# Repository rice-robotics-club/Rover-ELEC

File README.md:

# Rice Robotics URC Rover

Firmware, software, and hardware for Rice Robotics' [University Rover Challenge](https://urc.marssociety.org/) team.

<!-- TODO: rover photo or banner, e.g.  — keep it under ~500 KB -->

---

## About

The University Rover Challenge (URC) is an international competition, run by the Mars Society, where student teams design and build a Mars rover prototype. The rover competes in field missions such as science sample analysis, equipment servicing, extreme retrieval and delivery, and autonomous navigation. Check the current year's rules for the exact missions.

This repository holds all of our rover work. The current focus is the **2026-2027 season**.

- **Club website:** TODO
- **URC rules:** TODO (link to the current year's rules)

---

## Repository Layout

```
Rover-ELEC/
├── 2024-2025/              # archive
├── 2025-2026/              # archive
├── 2026-2027/              # current season
│   ├── rover-arm/
│   ├── rover-drivetrain/
│   ├── rover-science/
│   ├── rover-communication/
│   ├── rover-power/
│   └── rover-integration/
└── Summer26/               # archive
```

`2024-2025/`, `2025-2026/`, and `Summer26/` are kept as-is for reference. **All new work goes in `2026-2027/`.**

---

## Subsystems

| Subsystem | What it does | Lead |
|---|---|---|
| [rover-arm](2026-2027/rover-arm/) | Controls the Dynamixel and Robstride actuators on the arm for autonomous and teleop tasks | Joshua Aviles |
| [rover-drivetrain](2026-2027/rover-drivetrain/) | Controls the Robstrides on the drivetrain for autonomous and teleop tasks | Joshua Aviles |
| [rover-science](2026-2027/rover-science/) | Control and manage the sensors and actuators needed for science | Sean Drzewiczewski |
| [rover-communication](2026-2027/rover-communication/) | Establish the link between the radios on the rover and the base station | Sam Wilson |
| [rover-power](2026-2027/rover-power/) | Provide and manage the power needed for all subsystems and their individual components | Miles Kammler |
| [rover-integration](2026-2027/rover-integration/) | Connect all subsystems to the onboard computer under a single ROS workspace | Sam Wilson |

Not sure who to ask? Start with the subsystem lead.

---

## Subsystem Structure

Every subsystem except `rover-integration` uses the same layout. If you know one, you know them all. `rover-integration` has its own layout, described in [its README](2026-2027/rover-integration/).

```
rover-<subsystem>/
├── README.md
├── docs/
│   ├── architecture.md
│   ├── hardware.md
│   ├── software.md
│   ├── testing.md
│   └── media/
├── firmware/
│   ├── arduino-core/
│   │   └── <node-name>/
│   │       ├── README.md
│   │       └── <node-name>.ino
│   └── esp-idf/
│       └── <node-name>/
│           ├── README.md
│           ├── platformio.ini
│           └── src/
├── software/
│   ├── rover_<subsystem>_<function>/
│   └── dependencies.md
├── hardware/
│   ├── pcb/
│   └── mechanical/
└── scripts/
```

### What goes where

**`README.md`**: Start here. What the subsystem does, which boards it uses, and how to build and upload.

**`docs/`**: Everything someone needs to understand the subsystem without asking you.
- `architecture.md`: The big picture. Block diagram and how the pieces talk to each other.
- `hardware.md`: Power, wiring, and pinout. "Which wire goes where?"
- `software.md`: ROS 2 nodes, topics, parameters, and how to run them.
- `testing.md`: How things were tested, the results, and how each number was measured.
- `media/`: Small images used in the docs (diagrams, pinouts). Videos and photo dumps go on Google Drive or YouTube, linked from `media/README.md`.

**`firmware/`**: Code that runs on the microcontrollers. Each folder inside is one board's job, named by what it does (`joint-controller`, `power-monitor`), not by chip.
- `arduino-core/`: Arduino code, built and uploaded with the **Arduino IDE**. The `.ino` file must have the same name as its folder.
- `esp-idf/`: ESP-IDF code, built and uploaded with **PlatformIO**. When an Arduino node is ported to ESP-IDF, it keeps the same folder name.

**`software/`**: Code that runs on the Jetson.
- `rover_<subsystem>_<function>/`: One full ROS 2 package per folder (for example, `rover_arm_control`).
- `dependencies.md`: Outside libraries and tools this subsystem uses, with links and versions.

**`hardware/`**: Physical design files.
- `pcb/`: KiCad source files plus fabrication outputs (Gerbers, BOM, PDF schematic).
- `mechanical/`: CAD files, or links to Onshape/Fusion.

**`scripts/`**: Helper scripts for flashing, calibration, parsing logs, and similar tasks.

## Firmware README Template

Every firmware folder (`arduino-core/<node-name>/` or `esp-idf/<node-name>/`) needs a `README.md`. Copy this, fill in the table, and leave the hint comment in if you want (it doesn't show on GitHub).

```markdown
# node-name

Short 1-2 sentence summary of what this firmware does and what it connects to.

<!--
How to fill this in:
- Board: exact name from Tools > Board (Arduino IDE) or "board =" in platformio.ini
- Tool: Arduino IDE version (Help > About), or PlatformIO Core version (run: pio --version)
- Board package / platform: Arduino IDE > Boards Manager version, or "platform =" in platformio.ini
- Libraries: name + version, separated by <br> for multiple, or "None"
- Wiring: link to the pinout in docs/hardware.md
-->

| Field | Value |
|---|---|
| **Board** |  |
| **Tool** |  |
| **Board package / platform** |  |
| **Libraries** |  |
| **Wiring** | [docs/hardware.md](../../../docs/hardware.md) |
```

### Ground rules

- Don't delete folders your subsystem isn't using yet. Leave the stub `README.md` so every subsystem looks the same.
- Arduino IDE is only for `arduino-core/`, and PlatformIO is only for `esp-idf/`.
- Never commit build outputs (`.pio/`, `build/`, `install/`, `log/`) or large videos.

---

## Tech Stack

| Area | Standard |
|---|---|
| Onboard computer | NVIDIA Jetson, Ubuntu 24.04, ROS 2 Jazzy |
| Microcontrollers | Arduino (initial testing only) and ESP-32S |
| Firmware | Arduino core (Arduino IDE) or ESP-IDF (PlatformIO) |
| PCB design | KiCad |
| Mechanical CAD | Onshape |

---

## Getting Started

1. **Install git** and set up your GitHub account. Ask a lead to add you to the repo.
2. **Clone the repo:**
```bash
   git clone https://github.com/rice-robotics-club/Rover-ELEC.git
   cd Rover-ELEC 
```
3. **Install the tools for your subsystem:**
   - **Firmware (Arduino):** [Arduino IDE](https://www.arduino.cc/en/software) + the ESP32 board package
   - **Firmware (ESP-IDF):** [PlatformIO](https://platformio.org/install/ide?install=vscode) in VS Code
   - **ROS 2 / Jetson:** see [`rover-integration/docs/jetson-setup.md`](2026-2027/rover-integration/docs/jetson-setup.md)
   - **PCB:** [KiCad](https://www.kicad.org/download/) TODO (version)
4. **Read your subsystem's README** and [CONTRIBUTING.md](CONTRIBUTING.md) before your first commit.

---

## Contributing

1. Pull the latest `main`.
2. Create a branch: `<subsystem>/<short-description>` (example: `arm/joint-limits`).
3. Commit small, clear changes.
4. Open a pull request into `main`. Your subsystem lead will review it.

Never commit directly to `main`. Full rules are in [CONTRIBUTING.md](CONTRIBUTING.md).

---

## Resources

- **Google Drive (photos, videos, large files):** TODO
- **Discord / Slack:** TODO
- **URC rules:** TODO
- **Team docs / meeting notes:** TODO

---

## License

This project is licensed under the terms in [LICENSE](LICENSE).

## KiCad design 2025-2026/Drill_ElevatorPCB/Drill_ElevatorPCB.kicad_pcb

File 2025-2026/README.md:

# Rover-ELEC
Repo for all you rover elec fiends

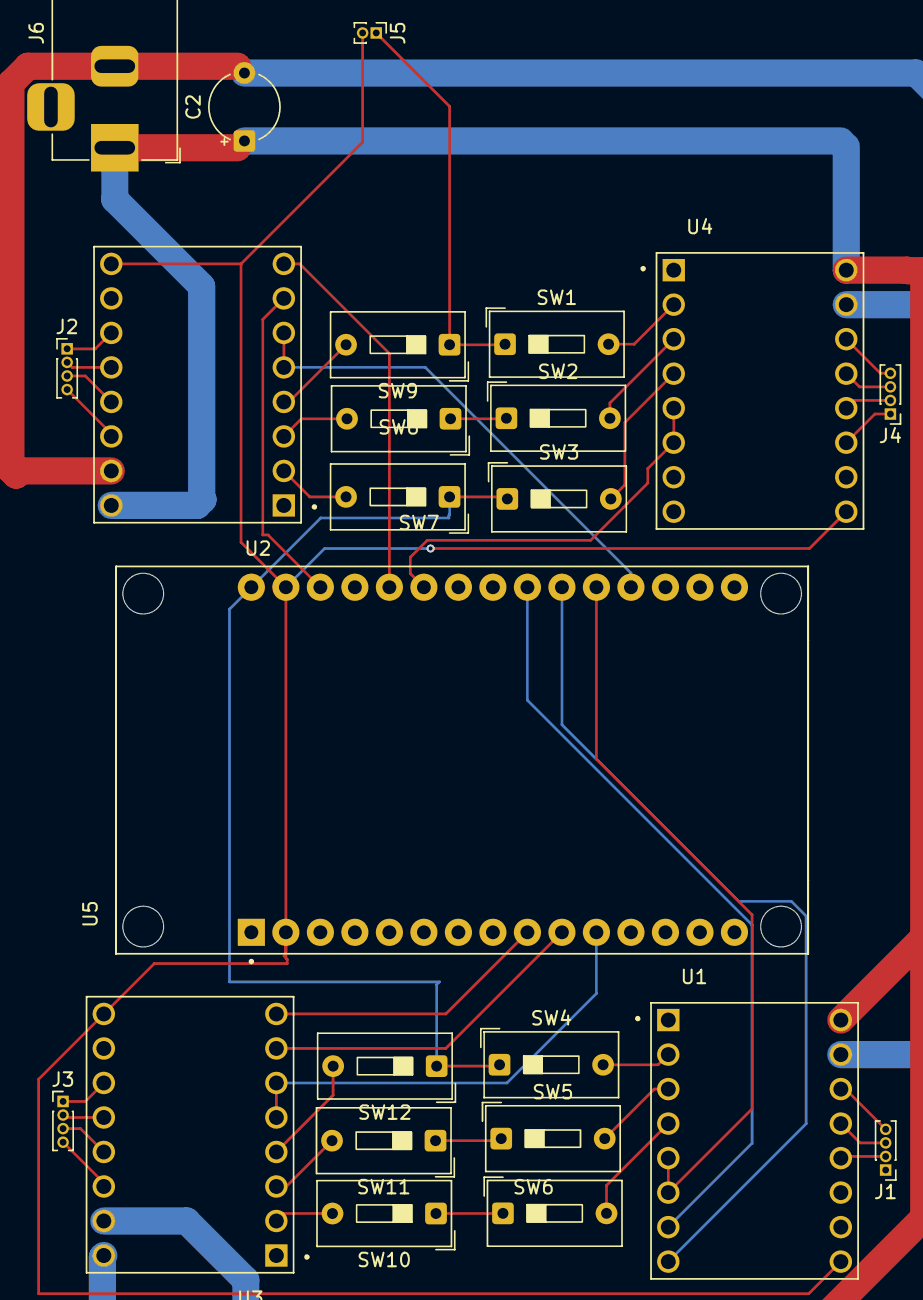
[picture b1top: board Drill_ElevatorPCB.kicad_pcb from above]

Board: 2 copper layers, 24 parts (0 on the bottom side), 44 nets.

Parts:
C2: C_Polarized; CP_Radial_Tantal_D5.0mm_P5.00mm
J1, J2, J3, J4: Conn_01x04_Socket; PinHeader_1x04_P1.00mm_Vertical
J5: Conn_01x02_Socket; PinHeader_1x02_P1.00mm_Vertical
J6: Barrel_Jack; BarrelJack_Horizontal
SW1, SW2, SW3, SW4, SW5, SW6, SW7, SW8, SW9, SW10, SW11, SW12: SW_DIP_x01; SW_DIP_SPSTx01_Slide_9.78x4.72mm_W7.62mm_P2.54mm
U1, U2, U3, U4: DRV8825_STEPPER_MOTOR_DRIVER_CARRIER; IC_DRV8825_STEPPER_MOTOR_DRIVER_CARRIER
U5: ESP32-DEVKIT-V1; MODULE_ESP32_DEVKIT_V1

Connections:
+3.3V: J5.1, SW1.1, SW2.1, SW3.1, SW4.1, SW5.1, SW6.1, SW7.1, SW8.1, SW9.1, SW10.1, SW11.1, SW12.1, U5.30 (VIN)
+12V: C2.1, J6.1, U1.16 (VMOT), U2.16 (VMOT), U3.16 (VMOT), U4.16 (VMOT)
GND: J5.2, U1.9 (GND), U2.9 (GND), U3.9 (GND), U4.9 (GND), U5.2 (GND), U5.29 (GND)
GND2: C2.2, J6.2, U1.15 (GND_MOT), U2.15 (GND_MOT), U3.15 (GND_MOT), U4.15 (GND_MOT)
unnamed: J1.1, U1.11 (A2)
unnamed: J1.2, U1.12 (A1)
unnamed: J1.3, U1.13 (B1)
unnamed: J1.4, U1.14 (B2)
unnamed: J2.1, U2.11 (A2)
unnamed: J2.2, U2.12 (A1)
unnamed: J2.3, U2.13 (B1)
unnamed: J2.4, U2.14 (B2)
unnamed: J3.1, U3.11 (A2)
unnamed: J3.2, U3.12 (A1)
unnamed: J3.3, U3.13 (B1)
unnamed: J3.4, U3.14 (B2)
unnamed: J4.1, U4.11 (A2)
unnamed: J4.2, U4.12 (A1)
unnamed: J4.3, U4.13 (B1)
unnamed: J4.4, U4.14 (B2)
unnamed: SW4.2, U1.2 (M0)
unnamed: SW5.2, U1.3 (M1)
unnamed: SW6.2, U1.4 (M2)
unnamed: SW7.2, U2.2 (M0)
unnamed: SW8.2, U2.3 (M1)
unnamed: SW9.2, U2.4 (M2)
unnamed: SW10.2, U3.2 (M0)
unnamed: SW11.2, U3.3 (M1)
unnamed: SW12.2, U3.4 (M2)
unnamed: SW1.2, U4.2 (M0)
unnamed: SW2.2, U4.3 (M1)
unnamed: SW3.2, U4.4 (M2)
SLP/RST 1: U1.5 (~RST), U1.6 (~SLP), U5.20 (D35)
SLP/RST 2: U2.5 (~RST), U2.6 (~SLP), U5.19 (D34)
SLP/RST 3: U3.5 (~RST), U3.6 (~SLP), U5.11 (D21)
SLP/RST 4: U4.5 (~RST), U4.6 (~SLP), U5.25 (D27)
dir_1: U1.8 (DIR), U5.21 (D32)
dir_2: U2.8 (DIR), U5.26 (D14)
dir_3: U3.8 (DIR), U5.9 (D18)
dir_4: U4.8 (DIR), U5.24 (D26)
step_1: U1.7 (STEP), U5.22 (D33)
step_2: U2.7 (STEP), U5.28 (D13)
step_3: U3.7 (STEP), U5.10 (D19)
step_4: U4.7 (STEP), U5.23 (D25)

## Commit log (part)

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2026-06-22 Some random movement code
2026-06-22 Small changes
2026-06-22 Organization
